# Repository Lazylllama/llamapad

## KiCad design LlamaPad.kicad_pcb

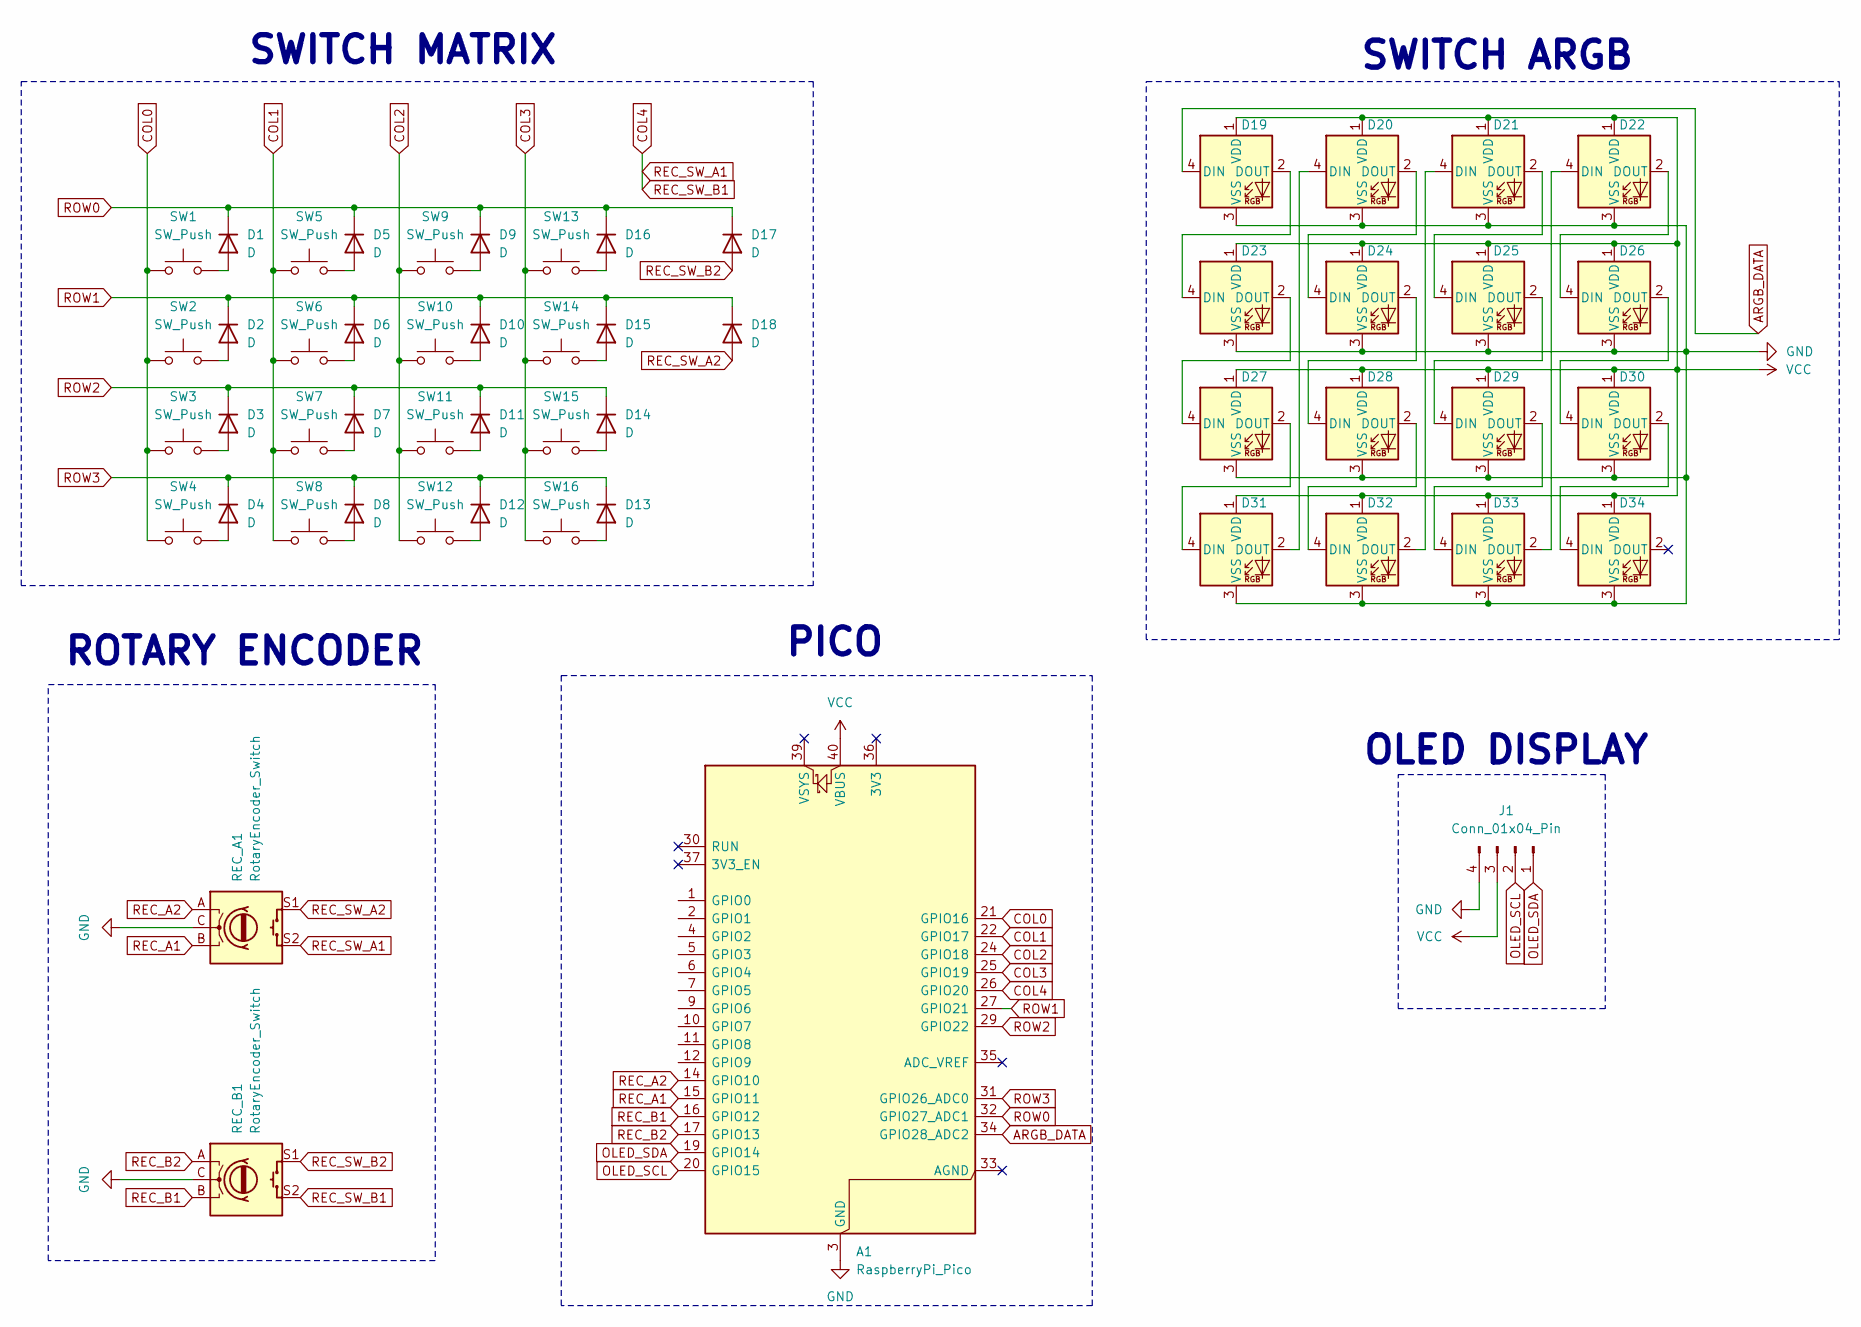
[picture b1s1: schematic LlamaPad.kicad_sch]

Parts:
A1: RaspberryPi_Pico; RaspberryPi_Pico_Common_Unspecified
D1, D2, D3, D4, D5, D6, D7, D8, D9, D10, D11, D12, D13, D14, D15, D16, D17, D18: D; D_DO-35_SOD27_P7.62mm_Horizontal
D19, D20, D21, D22, D23, D24, D25, D26, D27, D28, D29, D30, D31, D32, D33, D34: SK6812MINI-E; SK6812MINI-E_fixed
J1: Conn_01x04_Pin; PinHeader_1x04_P2.54mm_Vertical
REC_A1: RotaryEncoder_Switch; RotaryEncoder_Alps_EC11E-Switch_Vertical_H20mm
REC_B1: RotaryEncoder_Switch; RotaryEncoder_Alps_EC11E-Switch_Vertical_H20mm
SW1, SW2, SW3, SW4, SW5, SW6, SW7, SW8, SW9, SW10, SW11, SW12, SW13, SW14, SW15, SW16: SW_Push; MX-Hotswap-1U

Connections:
ARGB_DATA: A1.34 (GPIO28_ADC2), D19.4 (DIN)
COL0: A1.21 (GPIO16), SW1.1, SW2.1, SW3.1, SW4.1
COL1: A1.22 (GPIO17), SW5.1, SW6.1, SW7.1, SW8.1
COL2: A1.24 (GPIO18), SW9.1, SW10.1, SW11.1, SW12.1
COL3: A1.25 (GPIO19), SW13.1, SW14.1, SW15.1, SW16.1
COL4: A1.26 (GPIO20), REC_A1.S2, REC_B1.S2
GND: A1.3 (GND), A1.8 (GND), A1.13 (GND), A1.18 (GND), A1.23 (GND), A1.28 (GND), A1.38 (GND), D19.3 (VSS), D20.3 (VSS), D21.3 (VSS), D22.3 (VSS), D23.3 (VSS), D24.3 (VSS), D25.3 (VSS), D26.3 (VSS), D27.3 (VSS), D28.3 (VSS), D29.3 (VSS), D30.3 (VSS), D31.3 (VSS), D32.3 (VSS), D33.3 (VSS), D34.3 (VSS), J1.4, REC_A1.C, REC_B1.C
unnamed: D1.2 (A), SW1.2
unnamed: D2.2 (A), SW2.2
unnamed: D3.2 (A), SW3.2
unnamed: D4.2 (A), SW4.2
unnamed: D5.2 (A), SW5.2
unnamed: D6.2 (A), SW6.2
unnamed: D7.2 (A), SW7.2
unnamed: D8.2 (A), SW8.2
unnamed: D9.2 (A), SW9.2
unnamed: D10.2 (A), SW10.2
unnamed: D11.2 (A), SW11.2
unnamed: D12.2 (A), SW12.2
unnamed: D13.2 (A), SW16.2
unnamed: D14.2 (A), SW15.2
unnamed: D15.2 (A), SW14.2
unnamed: D16.2 (A), SW13.2
unnamed: D19.2 (DOUT), D23.4 (DIN)
unnamed: D20.4 (DIN), D31.2 (DOUT)
unnamed: D20.2 (DOUT), D24.4 (DIN)
unnamed: D21.4 (DIN), D32.2 (DOUT)
unnamed: D21.2 (DOUT), D25.4 (DIN)
unnamed: D22.4 (DIN), D33.2 (DOUT)
unnamed: D22.2 (DOUT), D26.4 (DIN)
unnamed: D23.2 (DOUT), D27.4 (DIN)
unnamed: D24.2 (DOUT), D28.4 (DIN)
unnamed: D25.2 (DOUT), D29.4 (DIN)
unnamed: D26.2 (DOUT), D30.4 (DIN)
unnamed: D27.2 (DOUT), D31.4 (DIN)
unnamed: D28.2 (DOUT), D32.4 (DIN)
unnamed: D29.2 (DOUT), D33.4 (DIN)
unnamed: D30.2 (DOUT), D34.4 (DIN)
OLED_SCL: A1.20 (GPIO15), J1.2
OLED_SDA: A1.19 (GPIO14), J1.1
REC_A1: A1.15 (GPIO11), REC_A1.B
REC_A2: A1.14 (GPIO10), REC_A1.A
REC_B1: A1.16 (GPIO12), REC_B1.B
REC_B2: A1.17 (GPIO13), REC_B1.A
REC_SW_A2: D18.2 (A), REC_A1.S1
REC_SW_B2: D17.2 (A), REC_B1.S1
ROW0: A1.32 (GPIO27_ADC1), D1.1 (K), D5.1 (K), D9.1 (K), D16.1 (K), D17.1 (K)
ROW1: A1.27 (GPIO21), D2.1 (K), D6.1 (K), D10.1 (K), D15.1 (K), D18.1 (K)
ROW2: A1.29 (GPIO22), D3.1 (K), D7.1 (K), D11.1 (K), D14.1 (K)
ROW3: A1.31 (GPIO26_ADC0), D4.1 (K), D8.1 (K), D12.1 (K), D13.1 (K)
VCC: A1.40 (VBUS), D19.1 (VDD), D20.1 (VDD), D21.1 (VDD), D22.1 (VDD), D23.1 (VDD), D24.1 (VDD), D25.1 (VDD), D26.1 (VDD), D27.1 (VDD), D28.1 (VDD), D29.1 (VDD), D30.1 (VDD), D31.1 (VDD), D32.1 (VDD), D33.1 (VDD), D34.1 (VDD), J1.3

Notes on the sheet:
ROTARY ENCODER
SWITCH ARGB
OLED DISPLAY
PICO
SWITCH MATRIX

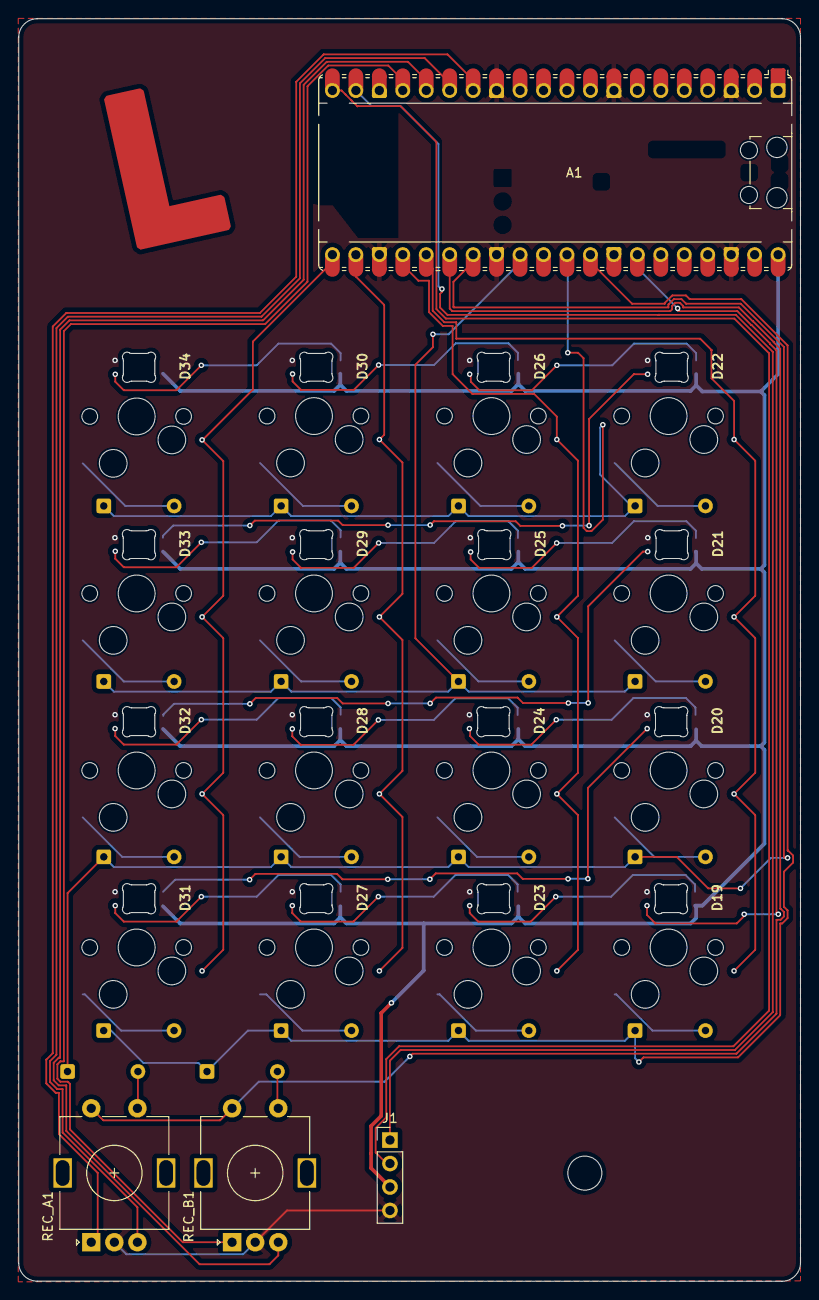
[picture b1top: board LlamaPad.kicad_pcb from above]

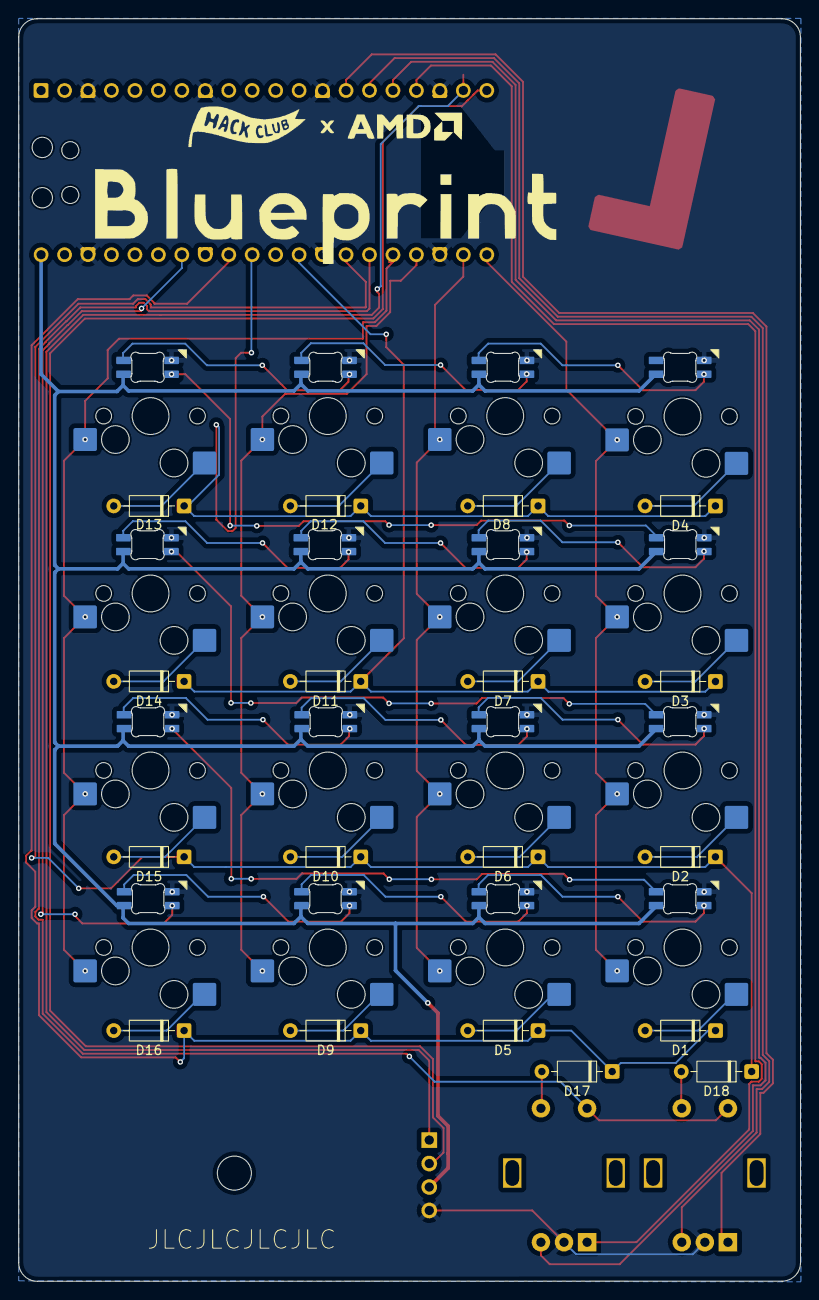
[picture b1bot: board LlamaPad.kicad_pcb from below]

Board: 2 copper layers, 84.6 x 136.7 mm, 54 parts (34 on the bottom side), 51 nets.

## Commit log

2026-02-18 feat: initial commit
2026-02-18 feat: add footprints
2026-02-18 feat: finish schematic rev1
2026-02-18 feat: add edge cuts
2026-02-19 feat: PCB rev1 (no traces)
2026-02-20 feat: footprint stuff
2026-02-22 feat: route the pcb and change schematic to be easier
